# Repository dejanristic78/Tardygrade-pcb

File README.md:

Controller PCB for the Tardygrade project. 
More info here: https://hackaday.io/project/180210-tardygrade

Developed using KiCad

For fabrication, use 1.6 mm pcb thickness.

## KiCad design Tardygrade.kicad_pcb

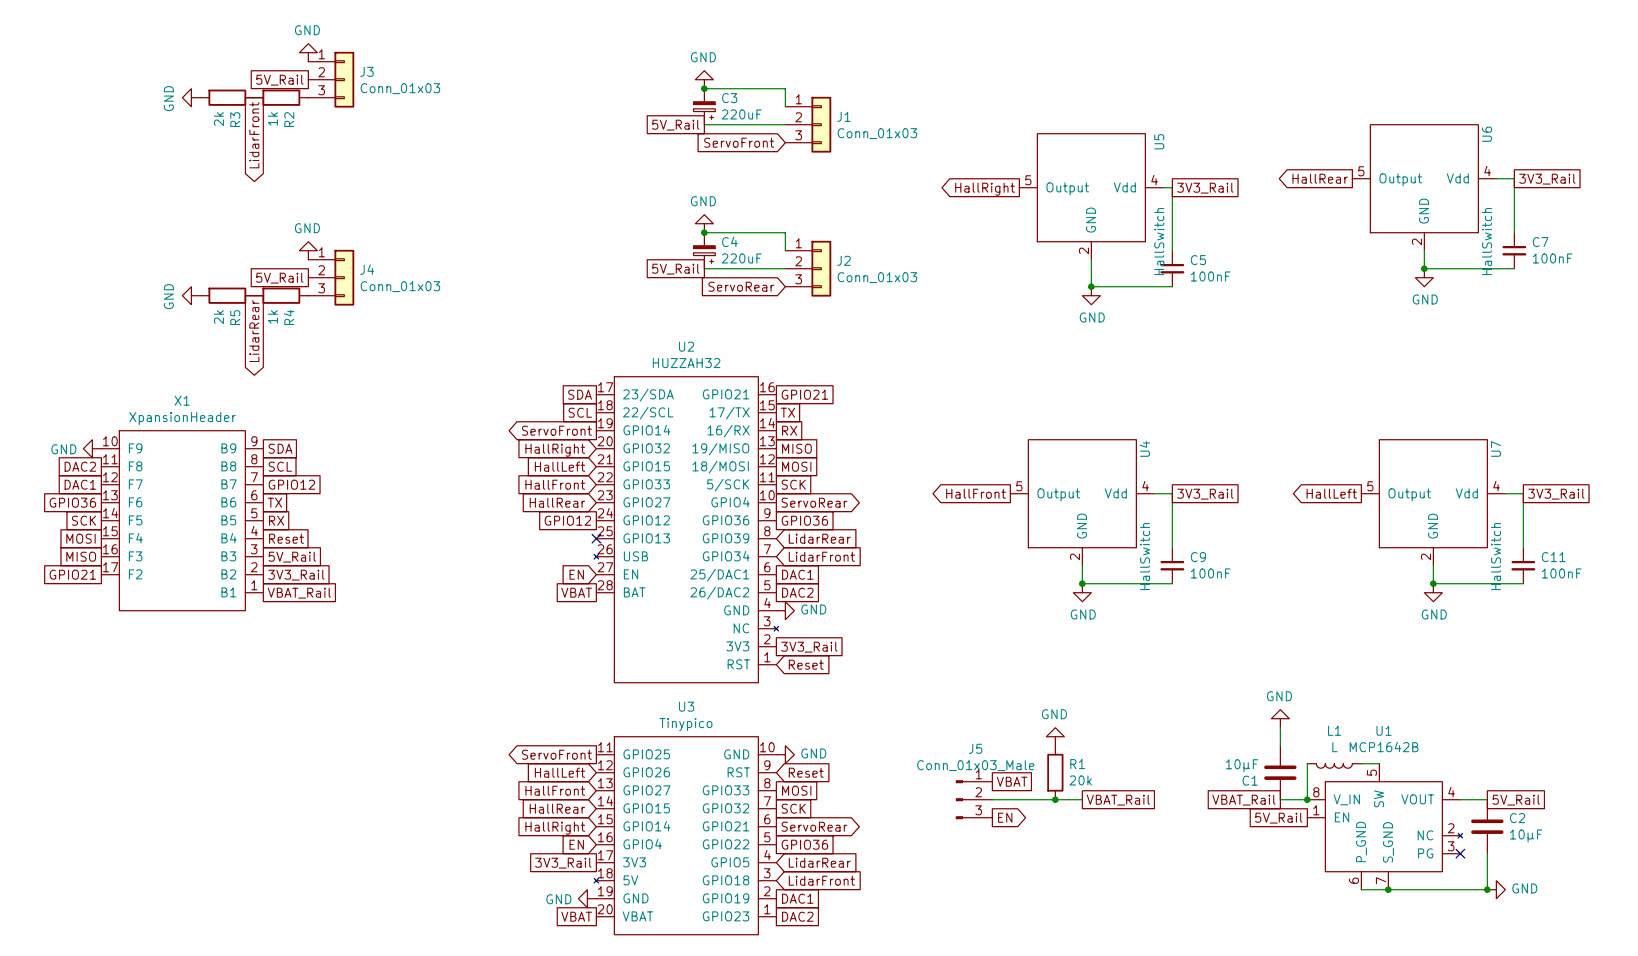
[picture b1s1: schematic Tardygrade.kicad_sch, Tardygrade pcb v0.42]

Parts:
C1, C2: 10μF; C_0603_1608Metric_HandSolderBig
C3, C4: 220uF; CP_Radial_D5.0mm_P2.00mm
C5, C7, C9, C11: 100nF; C_0603_1608Metric_Pad1.08x0.95mm_HandSolder
J1, J2, J3, J4: Conn_01x03; PinHeader_Servo
J5: Conn_01x03_Male; PinHeader_1x03_P2.54mm_Vertical
L1: L; 710-744052005
R1: 20k; R_0603_1608Metric_Pad0.98x0.95mm_HandSolder
R2, R4: 1k; R_0603_1608Metric_Pad0.98x0.95mm_HandSolder
R3, R5: 2k; R_0603_1608Metric_Pad0.98x0.95mm_HandSolder
U1: MCP1642B; MSOP-8_Handsolder
U2: HUZZAH32
U3: Tinypico
U4, U5, U6, U7: HallSwitch; SOT-553
X1: XpansionHeader

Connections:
3V3_Rail: C5.1, C7.1, C9.1, C11.1, U2.2 (3V3), U3.17 (3V3), U4.4 (Vdd), U5.4 (Vdd), U6.4 (Vdd), U7.4 (Vdd), X1.2 (B2)
5V_Rail: C2.1, C3.1, C4.1, J1.2, J2.2, J3.2, J4.2, U1.1 (EN), U1.4 (VOUT), X1.3 (B3)
DAC1: U2.6 (25/DAC1), U3.2 (GPIO19), X1.12 (F7)
DAC2: U2.5 (26/DAC2), U3.1 (GPIO23), X1.11 (F8)
EN: J5.3, U2.27 (EN), U3.16 (GPIO4)
GND: C1.2, C2.2, C3.2, C4.2, C5.2, C7.2, C9.2, C11.2, J1.1, J2.1, J3.1, J4.1, R1.1, R3.2, R5.2, U1.6 (P_GND), U1.7 (S_GND), U2.4 (GND), U3.10 (GND), U3.19 (GND), U4.2 (GND), U5.2 (GND), U6.2 (GND), U7.2 (GND), X1.10 (F9)
GPIO12: U2.24 (GPIO12), X1.7 (B7)
GPIO21: U2.16 (GPIO21), X1.17 (F2)
GPIO36: U2.9 (GPIO36), U3.5 (GPIO22), X1.13 (F6)
HallFront: U2.22 (GPIO33), U3.13 (GPIO27), U4.5 (Output)
HallLeft: U2.21 (GPIO15), U3.12 (GPIO26), U7.5 (Output)
HallRear: U2.23 (GPIO27), U3.14 (GPIO15), U6.5 (Output)
HallRight: U2.20 (GPIO32), U3.15 (GPIO14), U5.5 (Output)
LidarFront: R2.2, R3.1, U2.7 (GPIO34), U3.3 (GPIO18)
LidarRear: R4.2, R5.1, U2.8 (GPIO39), U3.4 (GPIO5)
MISO: U2.13 (19/MISO), X1.16 (F3)
MOSI: U2.12 (18/MOSI), U3.8 (GPIO33), X1.15 (F4)
unnamed: J3.3, R2.1
unnamed: J4.3, R4.1
unnamed: L1.1, U1.5 (SW)
RX: U2.14 (16/RX), X1.5 (B5)
Reset: U2.1 (RST), U3.9 (RST), X1.4 (B4)
SCK: U2.11 (5/SCK), U3.7 (GPIO32), X1.14 (F5)
SCL: U2.18 (22/SCL), X1.8 (B8)
SDA: U2.17 (23/SDA), X1.9 (B9)
ServoFront: J1.3, U2.19 (GPIO14), U3.11 (GPIO25)
ServoRear: J2.3, U2.10 (GPIO4), U3.6 (GPIO21)
TX: U2.15 (17/TX), X1.6 (B6)
VBAT: J5.1, U2.28 (BAT), U3.20 (VBAT)
VBAT_Rail: C1.1, J5.2, L1.2, R1.2, U1.8 (V_IN), X1.1 (B1)

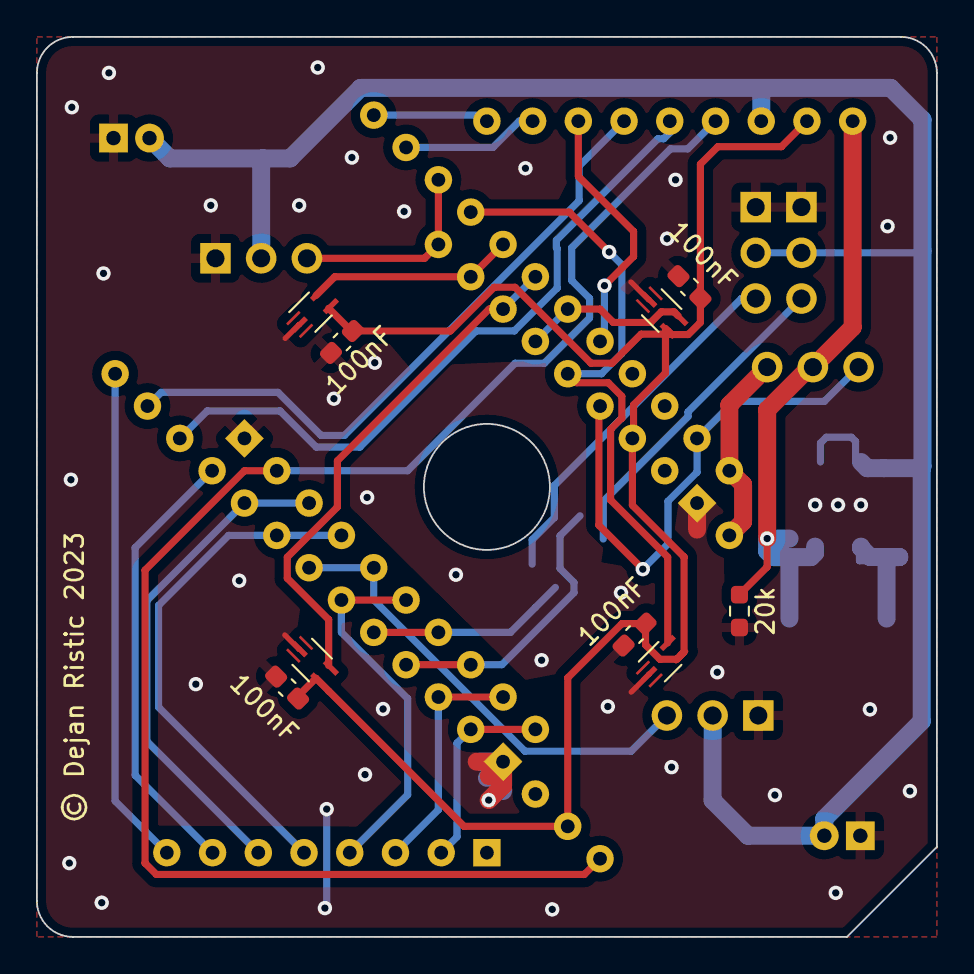
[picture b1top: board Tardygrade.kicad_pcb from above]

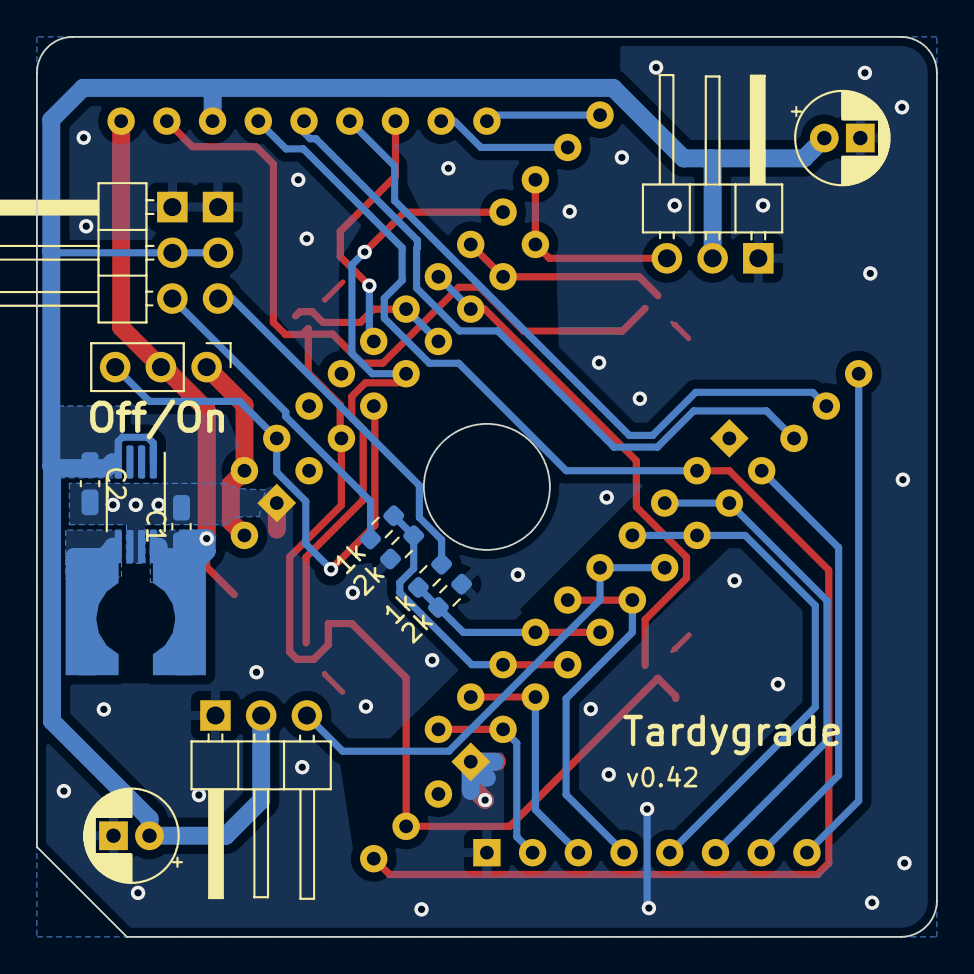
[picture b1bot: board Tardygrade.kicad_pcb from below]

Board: 2 copper layers, 50.0 x 50.0 mm, 27 parts (15 on the bottom side), 30 nets.

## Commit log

2021-09-24 Update README.md
    Updated readme
2021-09-24 pcb v0.3 Uses AH1815 hall switches
2021-10-09 New hall switch footprints
2021-10-11 Changed some GPIOs. Minor edits.
2021-10-11 Changed cap values for hall switches
2021-10-25 v0.4 update
2021-10-26 more work on v0.4
2021-10-26 v.04 update3
2021-10-26 v0.4 update 4
2021-10-27 v0.4 update 5
2021-11-08 Updated licence and readme
2021-11-21 Reassigned GPIO12 -> GPIO32 on Adafruit. New board v0.41
2023-02-18 Version 0.42

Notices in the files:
Tardygrade.kicad_pcb:
© Dejan Ristic 2023
